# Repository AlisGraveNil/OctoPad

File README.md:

# OctoPad
 8key macropad in a circle

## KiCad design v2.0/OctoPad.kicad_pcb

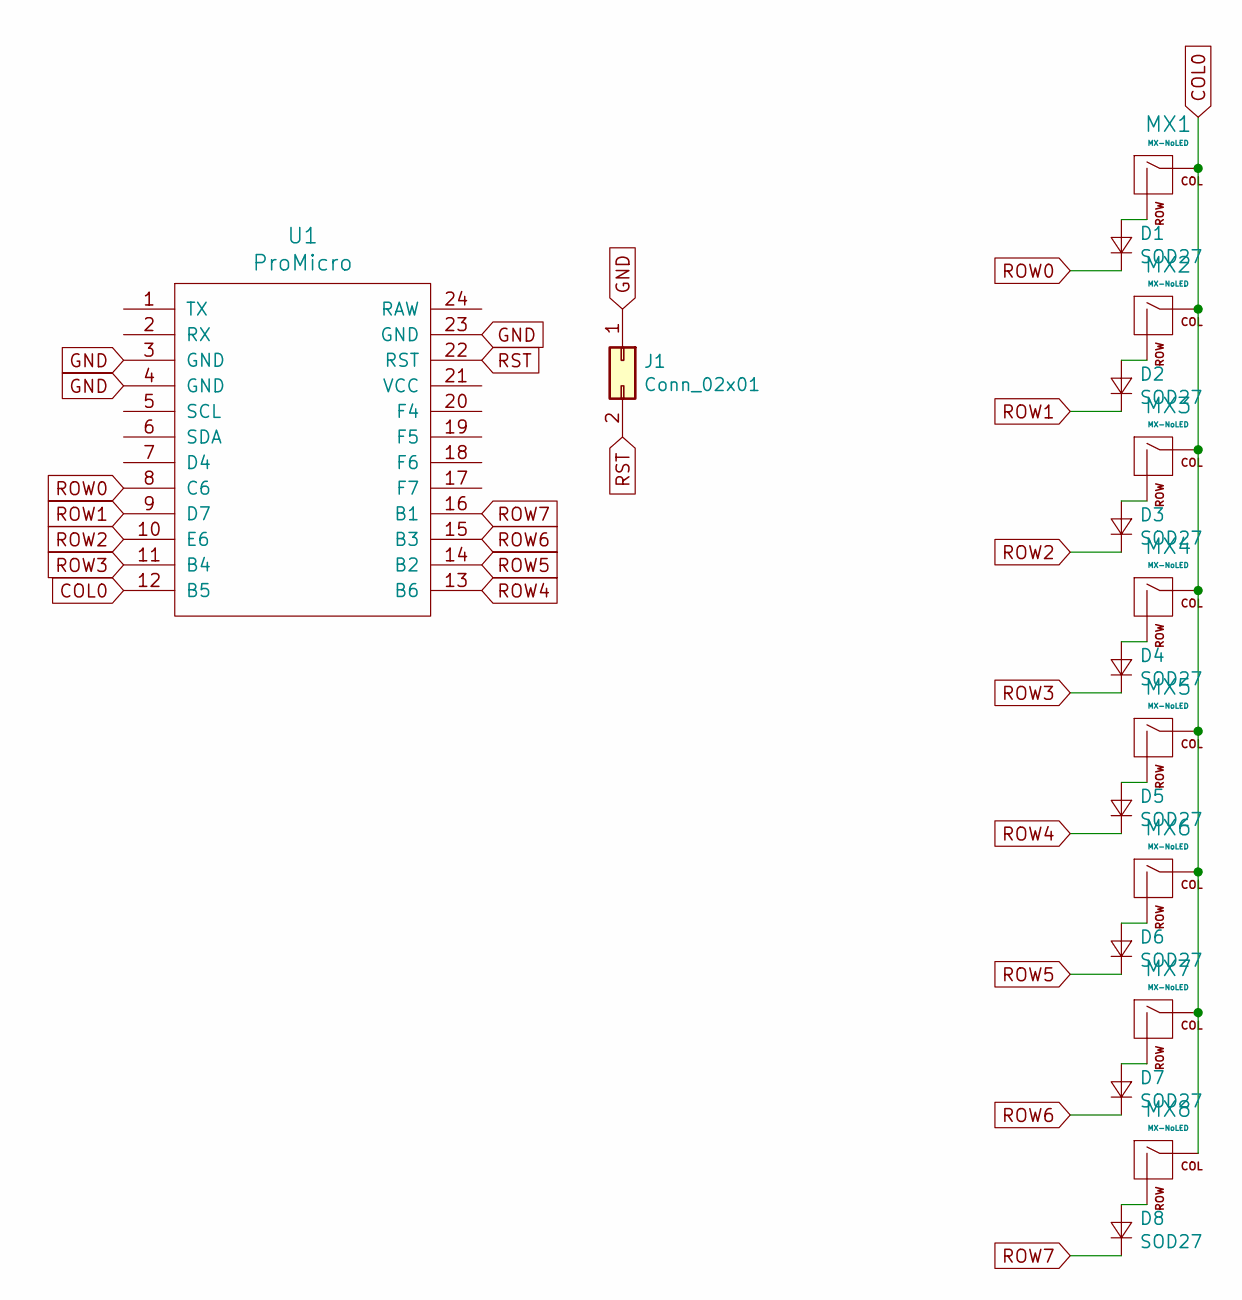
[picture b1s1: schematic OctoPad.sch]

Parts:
D1, D2, D3, D4, D5, D6, D7, D8: SOD27; D_DO-35_SOD27_P7.62mm_Horizontal
J1: Conn_02x01; SolderWirePad_1x02_P3.81mm_Drill0.8mm
MX1, MX2, MX3, MX4, MX5, MX6, MX7, MX8: MX-NoLED; MX-1U-NoLED
U1: ProMicro

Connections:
COL0: MX1.1 (COL), MX2.1 (COL), MX3.1 (COL), MX4.1 (COL), MX5.1 (COL), MX6.1 (COL), MX7.1 (COL), MX8.1 (COL), U1.12 (B5)
GND: J1.1, U1.3 (GND), U1.4 (GND), U1.23 (GND); also elsewhere on the board
unnamed: D1.2 (A), MX1.2 (ROW)
unnamed: D2.2 (A), MX2.2 (ROW)
unnamed: D3.2 (A), MX3.2 (ROW)
unnamed: D4.2 (A), MX4.2 (ROW)
unnamed: D5.2 (A), MX5.2 (ROW)
unnamed: D6.2 (A), MX6.2 (ROW)
unnamed: D7.2 (A), MX7.2 (ROW)
unnamed: D8.2 (A), MX8.2 (ROW)
ROW0: D1.1 (K), U1.8 (C6)
ROW1: D2.1 (K), U1.9 (D7)
ROW2: D3.1 (K), U1.10 (E6)
ROW3: D4.1 (K), U1.11 (B4)
ROW4: D5.1 (K), U1.13 (B6)
ROW5: D6.1 (K), U1.14 (B2)
ROW6: D7.1 (K), U1.15 (B3)
ROW7: D8.1 (K), U1.16 (B1)
RST: J1.2, U1.22 (RST); also elsewhere on the board

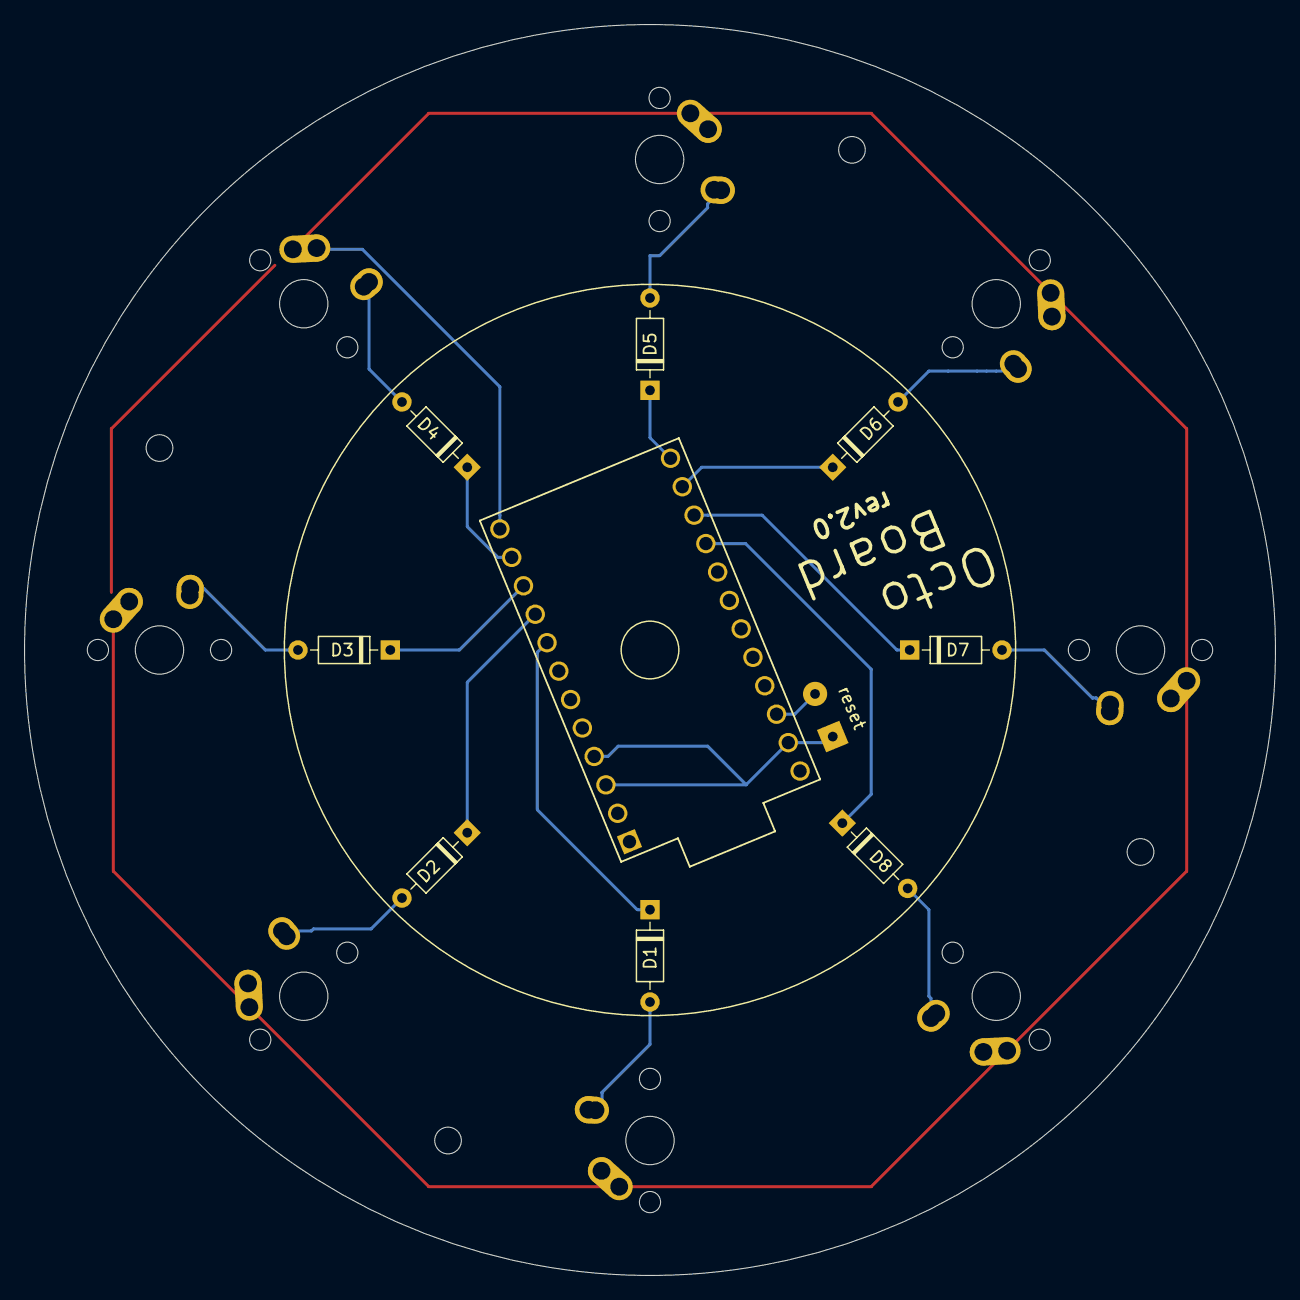
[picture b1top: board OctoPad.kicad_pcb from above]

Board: 2 copper layers, 103.2 x 103.2 mm, 18 parts (1 on the bottom side), 19 nets.

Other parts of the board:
reset: Conn_02x01; SolderWirePad_1x02_P3.81mm_Drill0.8mm

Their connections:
GND: reset.1; also elsewhere on the board
RST: reset.2; also elsewhere on the board

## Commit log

2020-04-04 4/4/20 v2
2020-04-05 4/5/20 v1
2020-04-05 4/5/20 v2
2020-04-06 4/6/20 v1
2020-04-06 4/6/20 v2
2020-04-22 4/22/20
2020-04-22 4/22/20 v3
